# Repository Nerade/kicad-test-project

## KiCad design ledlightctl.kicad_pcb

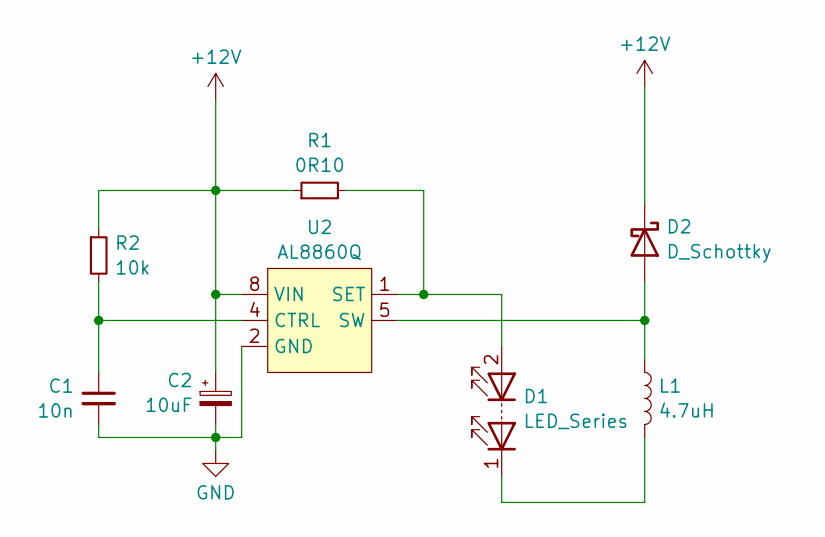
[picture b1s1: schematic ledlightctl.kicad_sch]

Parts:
C1: 10n
C2: 10uF
D1: LED_Series
D2: D_Schottky
L1: 4.7uH
R1: 0R10
R2: 10k
U2: AL8860Q

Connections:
+12V: C2.1, D2.1 (K), R1.1, R2.1, U2.8 (VIN)
GND: C1.2, C2.2, U2.2 (GND), U2.3 (GND)
unnamed: D1.2 (A), R1.2, U2.1 (SET)
unnamed: D1.1 (K), L1.2
unnamed: D2.2 (A), L1.1, U2.5 (SW), U2.6 (SW)
unnamed: C1.1, R2.2, U2.4 (CTRL)

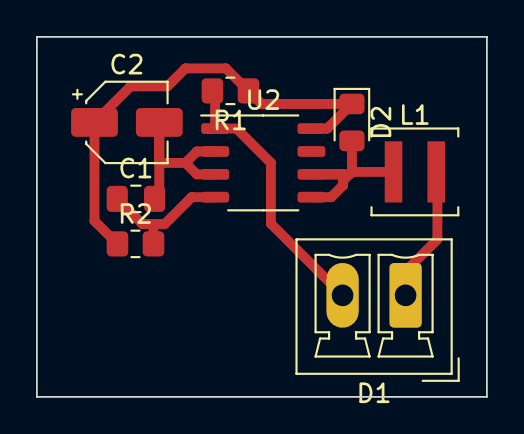
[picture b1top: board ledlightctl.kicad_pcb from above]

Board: 2 copper layers, 25.0 x 20.0 mm, 8 parts (0 on the bottom side), 6 nets.

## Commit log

2024-01-27 Panelize PCB
2024-01-27 Select footprints
2024-01-27 Add power connector Add copper zones
2024-01-27 Add control pin circuit
2024-01-27 Add GND copper pour
2024-01-27 First layout
